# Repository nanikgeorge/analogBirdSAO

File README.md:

# Analog Bird SAO
This is an SAO I designed to share at the Open Source Hardware Conference 2024.

It is my attempt at making an analog circuit that mimics a bird call, inspired by Kelly Heaton's work: [https://www.kellyheatonstudio.com/](https://www.kellyheatonstudio.com/)

What is an SAO? Here's a Hackaday article about that: [https://hackaday.com/2019/03/20/introducing-the-shitty-add-on-v1-69bis-standard/](https://hackaday.com/2019/03/20/introducing-the-shitty-add-on-v1-69bis-standard/)

The Open Hardware Summit (it was a lot of fun you should attend next year): [https://2024.oshwa.org/](https://2024.oshwa.org/)

The Open Hardware Summit is in Edinburgh next year! [https://2025.oshwa.org/](https://2025.oshwa.org/)

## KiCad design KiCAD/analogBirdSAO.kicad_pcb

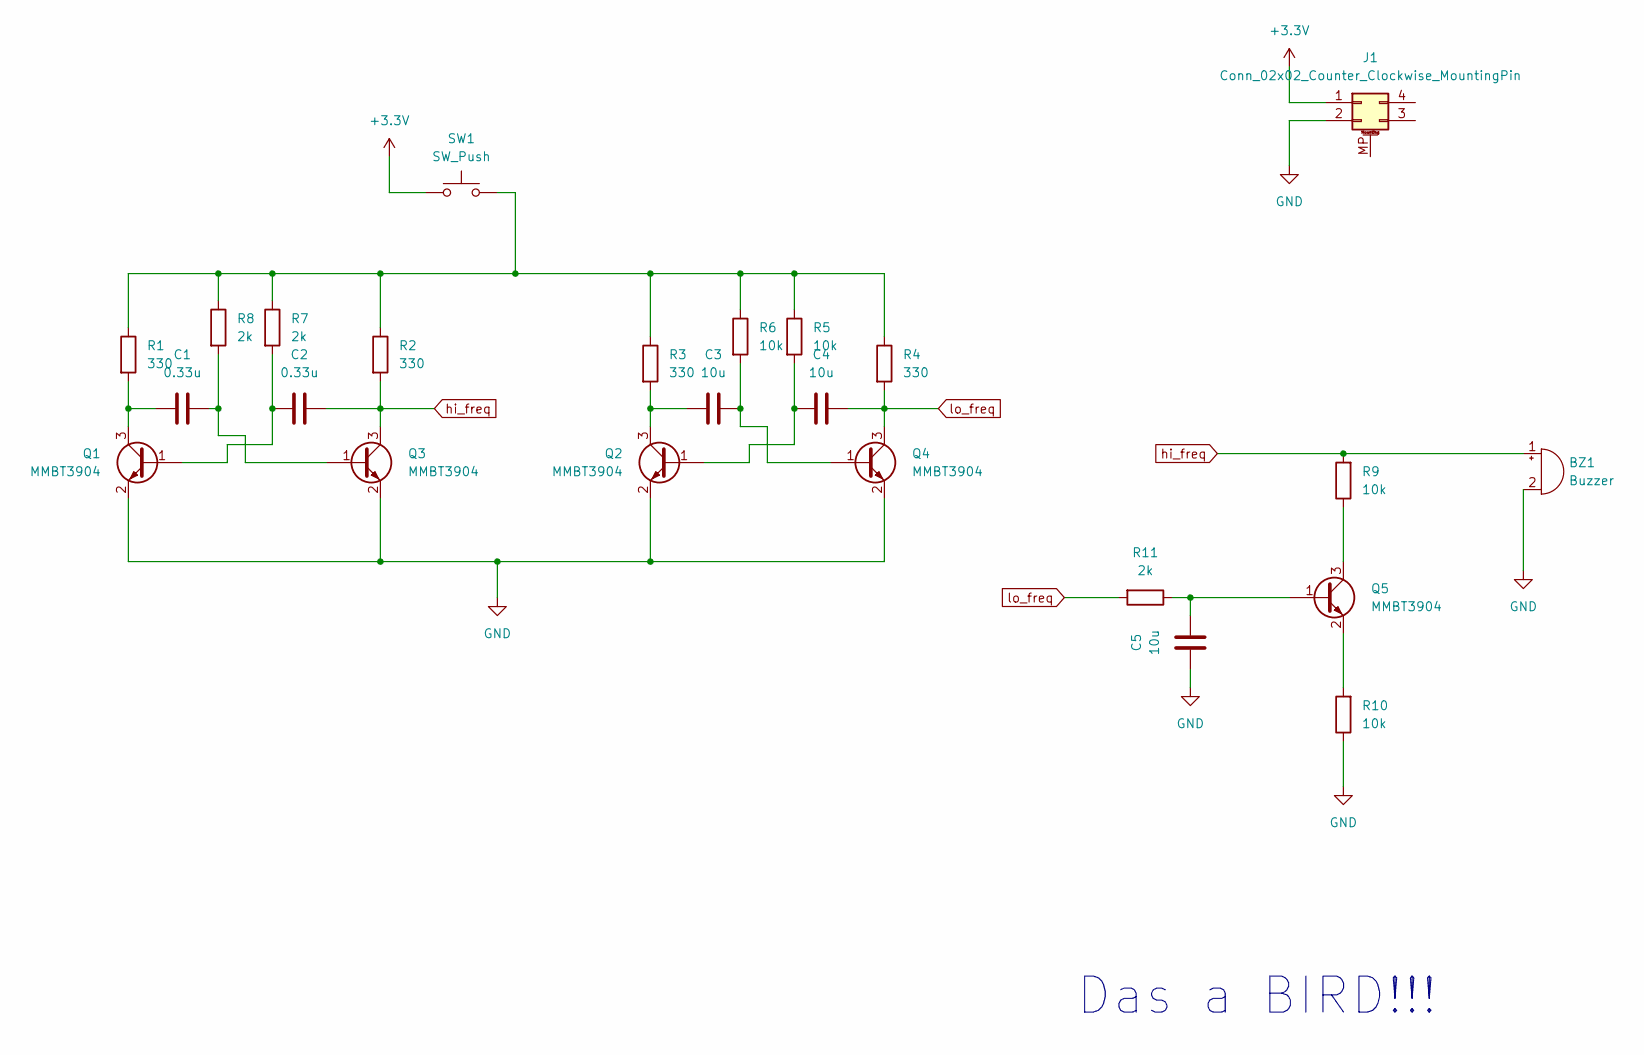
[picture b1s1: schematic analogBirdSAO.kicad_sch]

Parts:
BZ1: Buzzer; Buzzer_12x9.5RM7.6
C1, C2: 0.33u; C_0805_2012Metric
C3, C4, C5: 10u; C_0805_2012Metric
J1: Conn_02x02_Counter_Clockwise_MountingPin; PinHeader_2x02_P2.54mm_Vertical
Q1, Q2, Q3, Q4, Q5: MMBT3904; SOT-23
R1, R2, R3, R4: 330; R_0805_2012Metric
R5, R6, R9, R10: 10k; R_0805_2012Metric
R7, R8, R11: 2k; R_0805_2012Metric
SW1: SW_Push; SW_PUSH_6mm

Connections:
+3.3V: J1.1, SW1.1
GND: BZ1.2 (-), C5.1, J1.2, Q1.2 (E), Q2.2 (E), Q3.2 (E), Q4.2 (E), R10.1
unnamed: C2.1, Q1.1 (B), R7.2
unnamed: C1.1, Q1.3 (C), R1.2
unnamed: C4.1, Q2.1 (B), R5.2
unnamed: C3.1, Q2.3 (C), R3.2
unnamed: C1.2, Q3.1 (B), R8.2
unnamed: C3.2, Q4.1 (B), R6.2
unnamed: C5.2, Q5.1 (B), R11.1
unnamed: Q5.3 (C), R9.1
unnamed: Q5.2 (E), R10.2
unnamed: R1.1, R2.1, R3.1, R4.1, R5.1, R6.1, R7.1, R8.1, SW1.2
hi_freq: BZ1.1 (+), C2.2, Q3.3 (C), R2.2, R9.2
lo_freq: C4.2, Q4.3 (C), R4.2, R11.2

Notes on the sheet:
Das a BIRD!!!

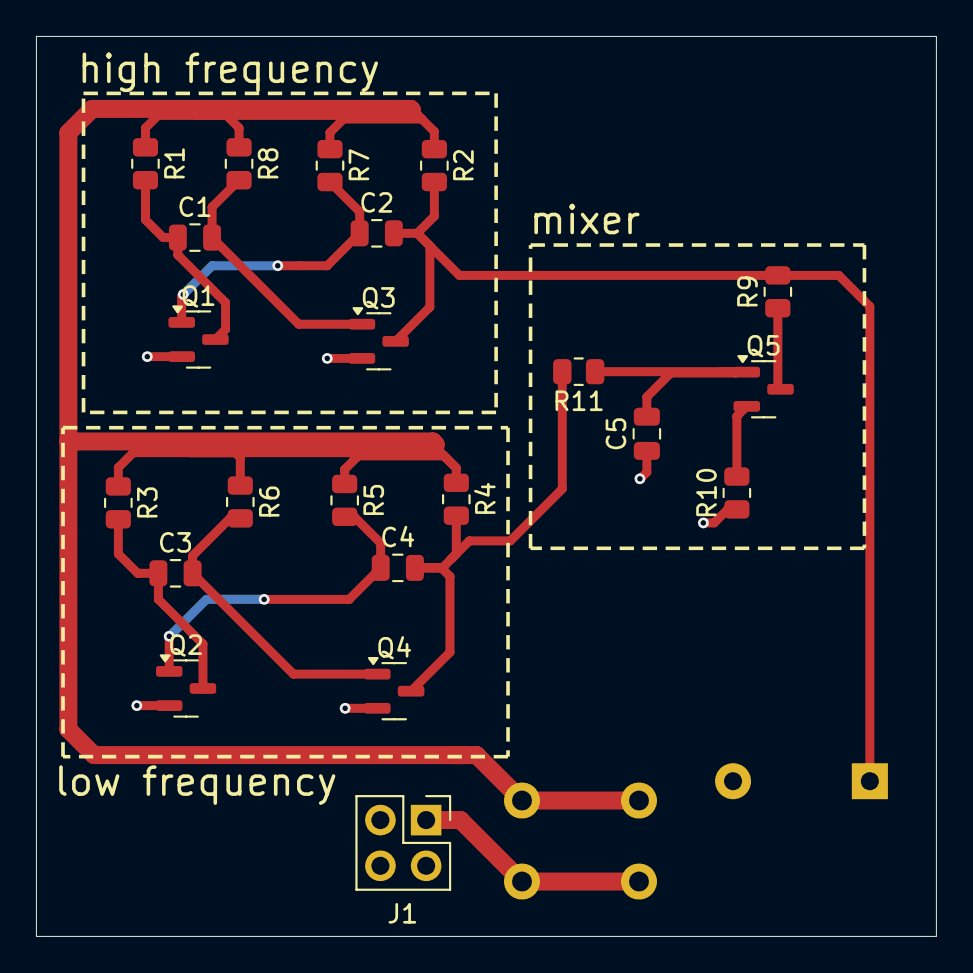
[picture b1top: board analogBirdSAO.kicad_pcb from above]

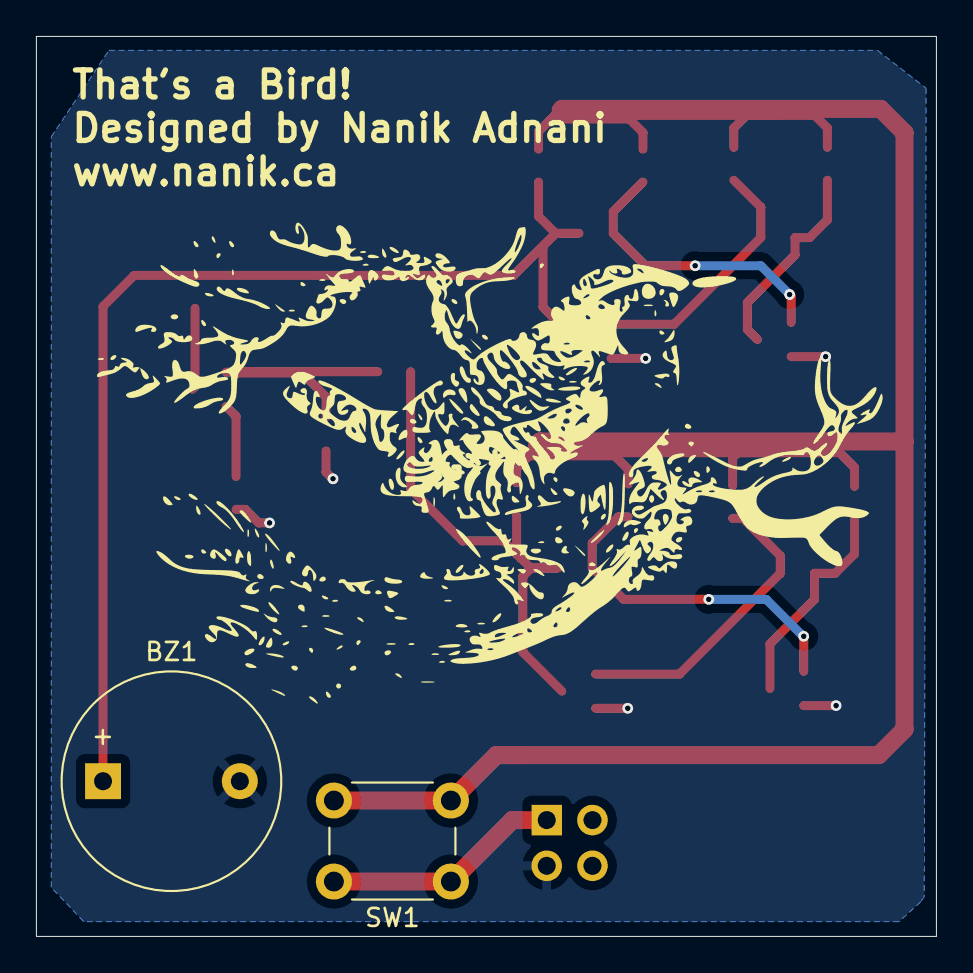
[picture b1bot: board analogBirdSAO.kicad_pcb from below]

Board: 2 copper layers, 50.0 x 50.0 mm, 24 parts (2 on the bottom side), 14 nets.

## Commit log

2024-07-11 added README
2024-11-08 added info for OHS 2025
2024-11-08 fixed README
